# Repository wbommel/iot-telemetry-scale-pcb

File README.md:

# IoT Telemetry Scale – PCB Design

This repository contains the KiCAD design files for the custom PCB used in the **IoT Telemetry Scale** project – a modular, networked weighing solution originally built to monitor the weights of budgies in an aviary. 🐦📡

The PCB is built around the **ESP8266 (ESP12-E/F)** and the **HX711** load cell amplifier, aiming to be compact, reliable, and easily integrated with MQTT-based telemetry systems.

---

## ⚠️ Disclaimer / Flaws

> 🛠 **This PCB was specifically designed for a personal, non-commercial project.**  
> It is tailored to the requirements of my own bird scale setup and may not meet broader standards or needs out of the box.

- The layout was created to match a 3D-printed housing (available as a FreeCAD project in a separate repository), designed to fit **one feeding station** in our aviary. 
- The **load cell** used is a **non-standard part salvaged from a consumer coin scale**. Mounting holes and electrical characteristics may not match typical off-the-shelf sensors.
- The PCB was optimized for simplicity and personal ease of assembly, not for mass production or universal compatibility.

> **👉 Adapt to your needs!**  
> If you intend to use different load cells, microcontrollers (ESP32, for example), or housing dimensions, expect to modify the schematic and board layout accordingly.

---

## 💾 Files Included

- `*.kicad_sch` – KiCAD schematic file
- `*.kicad_pcb` – PCB layout
- `*.lib` / `*.mod` – Custom symbols and footprints (if applicable)

---

## 🔧 Requirements

- Used KiCAD Version is [9.0.1](https://www.kicad.org/) (project not guaranteed to open cleanly in earlier versions)
- Familiarity with ESP8266 / HX711 modules
- Soldering tools and basic electronics skills

---

## 📦 Suggested Components

- **Microcontroller:** ESP8266 (ESP-12E or ESP-12F module)
- **Load Cell Amplifier:** HX711
- **Power Supply:** 5V micro-USB or regulated supply (depending on build)
- **Load Cell:** Use a standard model, often sold with appropriate HX711 module altogether

Note: Adjust footprints and layout to your needs.

---

## 📸 Related Projects

- [iot-telemetry-scale](https://github.com/wbommel/iot-telemetry-scale) - Meta repository
- [iot-telemetry-scale-firmware](https://github.com/wbommel/iot-telemetry-scale-firmware) – Firmware for this board

---

## 📜 License

This project is open source under the MIT License.  
Feel free to fork, modify, and improve!

---

## 🙏 Acknowledgements

Special thanks to the open hardware community and the creators of KiCAD for making electronics design accessible to everyone.

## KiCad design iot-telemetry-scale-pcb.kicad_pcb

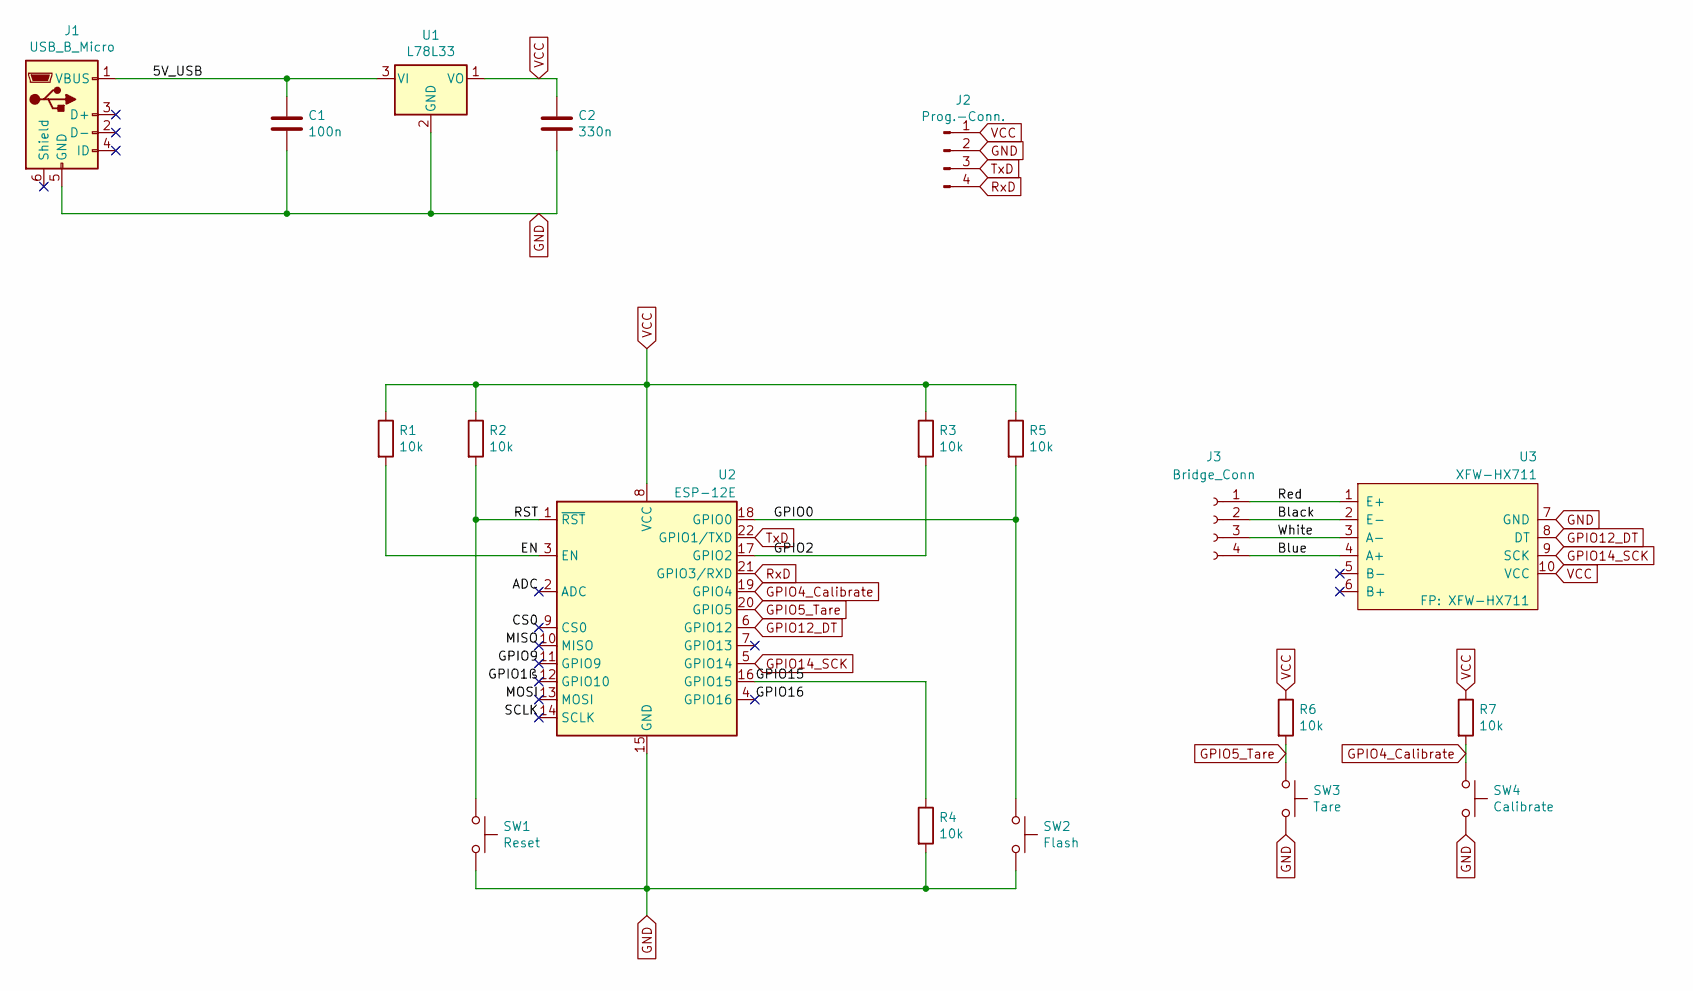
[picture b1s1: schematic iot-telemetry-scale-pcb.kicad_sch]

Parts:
C1: 100n; C_Disc_D6.0mm_W2.5mm_P5.00mm
C2: 330n; C_Rect_L9.0mm_W2.5mm_P7.50mm_MKT
J1: USB_B_Micro; USB_B_Micro_Breakout
J2: Prog.-Conn.; PinHeader_2x02_P2.54mm_Vertical
J3: Bridge_Conn; PinHeader_1x04_P2.54mm_Vertical
R1, R2, R3, R4, R5, R6, R7: 10k; R_Axial_DIN0207_L6.3mm_D2.5mm_P7.62mm_Horizontal
SW1: Reset; SW_PUSH_6mm
SW2: Flash; SW_PUSH_6mm
SW3: Tare; SW_PUSH_6mm
SW4: Calibrate; SW_PUSH_6mm
U1: L78L33; TO-92L_Inline_Wide
U2: ESP-12E
U3: XFW-HX711

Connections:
/5V_USB: C1.1, J1.1 (VBUS), U1.3 (VI)
/ADC: U2.2 (ADC)
/Black: J3.2, U3.2 (E-)
/Blue: J3.4, U3.4 (A+)
/CS0: U2.9 (CS0)
/EN: R1.2, U2.3 (EN)
/GPIO0: R5.2, SW2.1, U2.18 (GPIO0)
/GPIO1ß: U2.12 (GPIO10)
/GPIO2: R3.2, U2.17 (GPIO2)
/GPIO9: U2.11 (GPIO9)
/GPIO15: R4.1, U2.16 (GPIO15)
/GPIO16: U2.4 (GPIO16)
/MISO: U2.10 (MISO)
/MOSI: U2.13 (MOSI)
/RST: R2.2, SW1.1, U2.1 (~RST)
/Red: J3.1, U3.1 (E+)
/SCLK: U2.14 (SCLK)
/White: J3.3, U3.3 (A-)
GND: C1.2, C2.2, J1.5 (GND), J2.2, R4.2, SW1.2, SW2.2, SW3.2, SW4.2, U1.2 (GND), U2.15 (GND), U3.7 (GND)
GPIO4_Calibrate: R7.2, SW4.1, U2.19 (GPIO4)
GPIO5_Tare: R6.2, SW3.1, U2.20 (GPIO5)
GPIO12_DT: U2.6 (GPIO12), U3.8 (DT)
GPIO14_SCK: U2.5 (GPIO14), U3.9 (SCK)
RxD: J2.4, U2.21 (GPIO3/RXD)
TxD: J2.3, U2.22 (GPIO1/TXD)
VCC: C2.1, J2.1, R1.1, R2.1, R3.1, R5.1, R6.1, R7.1, U1.1 (VO), U2.8 (VCC), U3.10 (VCC)

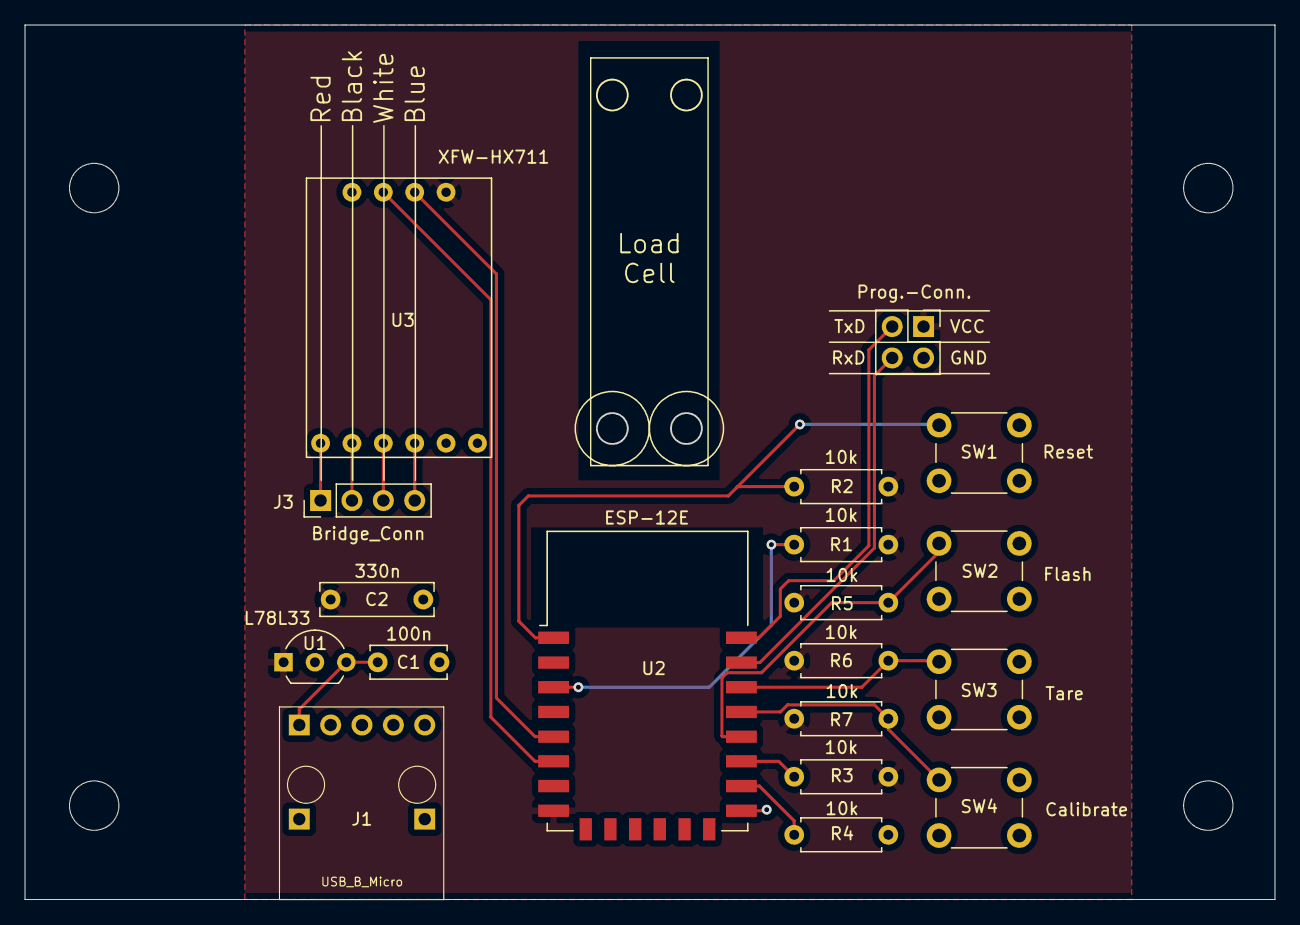
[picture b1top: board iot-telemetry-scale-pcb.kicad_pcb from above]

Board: 2 copper layers, 101.1 x 70.7 mm, 19 parts (0 on the bottom side), 18 nets.

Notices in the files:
iot-telemetry-scale-pcb.kicad_pcb:
(c) 2022 Volker Brömmel
